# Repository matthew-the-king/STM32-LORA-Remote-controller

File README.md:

THE PROJECT
This is my LORA radio controller project! I wanted to make this because I am currently building a drone
that requires a capable LORA radio.
I have posted the Gerber files and BOM so you can produce your own functioning LORA radio controller.
The controller has two joysticks, two switches, and two potentiometers for inputs.  I also added
a buzzer to notify people when events happen, like connecting to a device.  In the PCB step file I added all the 3d 
models I could, but I could not get the potentiometer's 3d models. 

BUILDING 
To build this PCB, I would recommend ordering the PCB with a stencil because of the small and closely located parts on the board.
This PCB uses parts with pads exposed ONLY on the underside!
The PCB BOM does not include the REQUIRED RYLR998 LORA module; you can buy this on [Amazon](https://www.amazon.com/REYAX-RYLR998-Interface-Antenna-Transceiver/dp/B099RM1XMG/ref=sr_1_1?crid=3UDNJM86BEADO&dib=eyJ2IjoiMSJ9.TrUCyGx0qarh1587JZE8yvvpoC9gwe9bI9YRw3IJh5Zx1KMgEmUzJjvn7MXzx70qEOTY9Fq1M7de8QXRClEF1gXgdkHaO5Cp1hr_cBkrCVVQM3ZOe9HBNgby4LxkEoifRjcGB3QqjgsQhcNnanCQkIOsF3Hd2hs2Dmw3LSlU7O13KyXTs3yf6Vi8z0KqYX-fim7_xzP2ZXnVLrSlw5k8YtSw-LhxjmDXxdbevTJhjuQ.NWGx5ZOZ6Yl5I9t_tEakvIQr32iyknbT6vLo_iMR5xk&dib_tag=se&keywords=rylr998&qid=1781199705&sprefix=RYLR%2Caps%2C197&sr=8-1). 
Place the Lora module in these pins  with the correct orientation according to the labeled pin on the module.
Here is the BOM, but you can also find the BOM.csv file in the repository:
| Designator | Footprint | Qty | Value | LCSC Part # |
|------------|-----------|-----|-------|-------------|
| BT1 | PinHeader_1x02_P2.54mm_Vertical | 1 | Battery_Cell | |
| C1, C16 | 0402 | 2 | 10uF | |
| C10, C9 | 0603 | 2 | 18pF | |
| C11, C15, C2, C3, C4, C8 | 0402 | 6 | 0.1uF | |
| C12, C6, C7 | 0805 | 3 | 1uF | |
| C13, C14 | 0603 | 2 | 4.7uF | |
| C5 | 0603 | 1 | 10nF | |
| D1, D2 | 0805 | 2 | LED | |
| D3 | 0603 | 1 | LED | |
| D4, D5 | LED_D5.0mm | 2 | LED | |
| F1 | CP_EIA-3528-12_Kemet-T | 1 | 22uF | |
| J1 | SAMESKY_UJ20-C-H-G-SMT-1-P16-TR | 1 | USB-C | |
| J2 | PinHeader_1x05_P2.54mm_Vertical | 1 | Conn_01x05_Socket | |
| J3 | PinHeader_1x05_P2.54mm_Vertical | 1 | Conn_01x05_Pin | |
| J4 | PinHeader_1x03_P2.54mm_Vertical | 1 | Conn_01x03_Pin | |
| L1 | 0603 | 1 | 120R | |
| LS1 | SPKR_PKM22EPPH4001-B0 | 1 | PKM22EPPH4001-B0 | |
| Q1, Q2 | SOT-23 | 2 | BSS806N | |
| R1 | 0603 | 1 | 39 | |
| R10, R11 | 0402 | 2 | 1k | |
| R12 | 0603 | 1 | 49.9K | |
| R13 | 0402 | 1 | 200k | |
| R14 | 0402 | 1 | 1.13K | |
| R15, R16 | POT_P120PK-x25_TTE | 2 | P120PK | |
| R17, R18, R19, R6 | 0402 | 4 | 10k | |
| R2, R3 | 0402 | 2 | 5.1k | |
| R20, R21 | 1206 | 2 | 5M | |
| R22, R23, R8 | 0603 | 3 | 330 | |
| R4, R5 | 0402 | 2 | 22 | |
| R7 | 0603 | 1 | 2.2k | |
| R9 | 0402 | 1 | 1.18k | |
| S1, S2 | SW_200MSP1T2B4M2QE | 2 | 200MSP1T2B4M2QE | |
| U1 | UFQFPN-48_7X7X0P55MM | 1 | STM32F103CBU6 | |
| U2 | SON50P150X150X80-6N | 1 | BQ29700DSER | |
| U3, U4 | XDCR_COM-09032 | 2 | Joy_Stick | |
| U5 | SOT-23-6 | 1 | USBLC6-2SC6 | |
| U6 | SOT-223-3_TabPin2 | 1 | AMS1117-3.3 | |
| U7 | QFN50P300X300X100-17N | 1 | BQ24072TRGTR | |
| Y1 | XTAL_ECS-240-8-33-AGN-TR | 1 | ECS-80-12-33-JGN-TR | |

Once you complete your PCB, you can 3d print a case!  The case is only two parts, a Base and a top that can be screwed together with 4, 20mm screws, also the base has some holes for threaded inserts for m2.

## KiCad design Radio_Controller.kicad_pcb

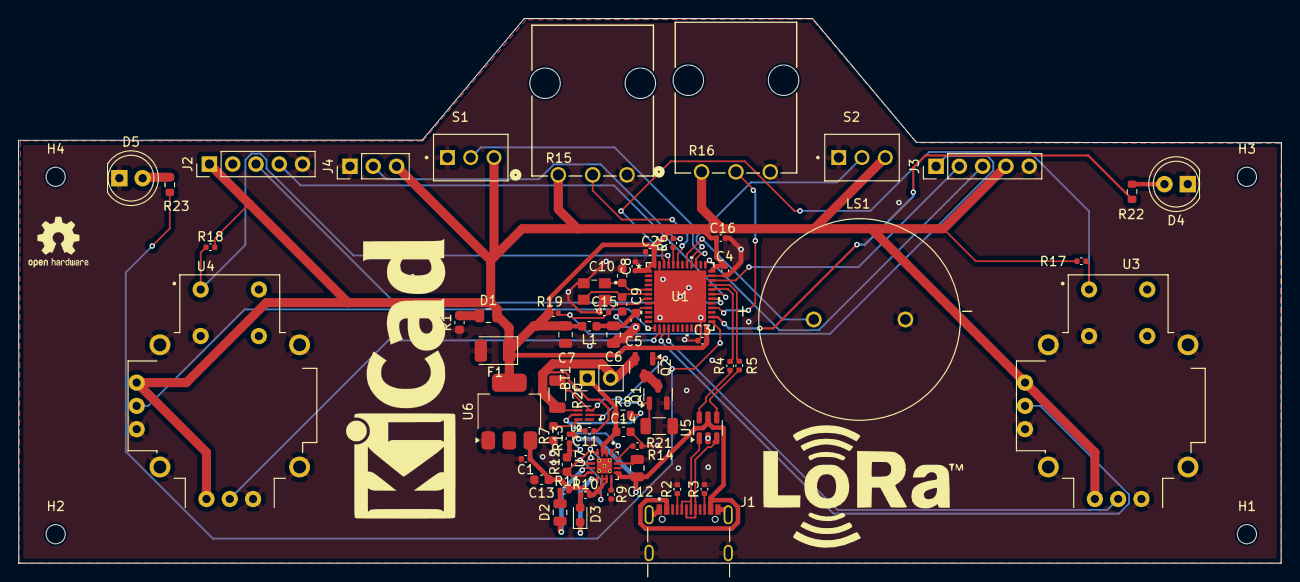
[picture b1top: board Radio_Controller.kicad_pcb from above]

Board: 2 copper layers, 137.8 x 59.4 mm, 68 parts (0 on the bottom side), 52 nets.

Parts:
BT1: Battery_Cell; PinHeader_1x02_P2.54mm_Vertical
C1, C16: 10uF; C_0402_1005Metric
C2, C3, C4, C8, C11, C15: 0.1uF; C_0402_1005Metric
C5: 10nF; C_0603_1608Metric
C6, C7, C12: 1uF; C_0805_2012Metric
C9, C10: 18pF; C_0603_1608Metric
C13, C14: 4.7uF; C_0603_1608Metric
D1, D2: LED; C_0805_2012Metric
D3: LED; LED_0603_1608Metric
D4, D5: LED; LED_D5.0mm
F1: 22uF; CP_EIA-3528-12_Kemet-T
H1, H2, H3, H4: MountingHole; MountingHole_2.1mm
J1: USB-C; SAMESKY_UJ20-C-H-G-SMT-1-P16-TR
J2: Conn_01x05_Socket; PinHeader_1x05_P2.54mm_Vertical
J3: Conn_01x05_Pin; PinHeader_1x05_P2.54mm_Vertical
J4: Conn_01x03_Pin; PinHeader_1x03_P2.54mm_Vertical
L1: 120R; C_0603_1608Metric
LS1: PKM22EPPH4001-B0; SPKR_PKM22EPPH4001-B0
Q1, Q2: BSS806N; SOT-23
R1: 39; C_0603_1608Metric
R2, R3: 5.1k; C_0402_1005Metric
R4, R5: 22; C_0402_1005Metric
R6, R17, R18, R19: 10k; C_0402_1005Metric
R7: 2.2k; C_0603_1608Metric
R8, R22, R23: 330; R_0603_1608Metric
R9: 1.18k; C_0402_1005Metric
R10, R11: 1k; C_0402_1005Metric
R12: 49.9K; C_0603_1608Metric
R13: 200k; C_0402_1005Metric
R14: 1.13K; C_0402_1005Metric
R15, R16: P120PK; POT_P120PK-x25_TTE
R20, R21: 5M; C_1206_3216Metric
S1, S2: 200MSP1T2B4M2QE; SW_200MSP1T2B4M2QE
U1: STM32F103CBU6; UFQFPN-48_7X7X0P55MM
U2: BQ29700DSER; SON50P150X150X80-6N
U3, U4: Joy_Stick; XDCR_COM-09032
U5: USBLC6-2SC6; SOT-23-6
U6: AMS1117-3.3; SOT-223-3_TabPin2
U7: BQ24072TRGTR; QFN50P300X300X100-17N
Y1: ECS-80-12-33-JGN-TR; XTAL_ECS-240-8-33-AGN-TR

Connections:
+3.3V: C2.2, C3.2, C4.2, C7.1, C8.2, C16.2, D1.2 (A), F1.1, J2.1, J3.4, J4.3, L1.2, R15.1, R16.1, R17.2, R18.2, R19.2, S1.3, S2.3, U1.1 (VBAT), U1.24 (VDD_1), U1.36 (VDD_2), U1.48 (VDD_3), U3.H1 (H+), U3.V1 (V+), U4.H1 (H+), U4.V1 (V+), U6.2 (VO)
BOOT0: J4.2, R6.2
D+: R5.2, U1.33 (PA12)
D-: R4.2, U1.32 (PA11)
GND: C1.2, C2.1, C3.1, C4.1, C5.2, C6.2, C7.2, C8.1, C9.1, C10.1, C12.2, C13.2, C14.2, C15.1, C16.1, D4.1 (K), D5.1 (K), F1.2, J1.A1_B12 (GND), J1.B1_A12 (GND__1), J1.SH1 (SHIELD), J1.SH2 (SHIELD__1), J1.SH3 (SHIELD__2), J1.SH4 (SHIELD__3), J2.5, J3.5, J4.1, LS1.N, Q1.2 (S), R1.1, R2.2, R3.2, R7.1, R9.2, R12.2, R14.2, R15.3, R16.3, R21.1, S1.1, S2.1, U1.8 (VSSA), U1.23 (VSS_1), U1.35 (VSS_2), U1.47 (VSS_3), U1.49 (EPAD), U3.B2A (SEL-), U3.H3 (H-), U3.S1 (SHIELD), U3.S2 (SHIELD__1), U3.S3 (SHIELD__2), U3.S4 (SHIELD__3), U3.V3 (V-), U4.B2A (SEL-), U4.H3 (H-), U4.S1 (SHIELD), U4.S2 (SHIELD__1), U4.S3 (SHIELD__2), U4.S4 (SHIELD__3), U4.V3 (V-), U5.2 (GND), U6.1 (GND), U7.4 (~CE), U7.6 (EN1), U7.8 (VSS), U7.15 (TD), U7.17 (EP), Y1.2 (GND), Y1.4 (GND__1)
H1: U1.14 (PA4), U4.H2 (H)
H2: U1.16 (PA6), U3.H2 (H)
NRST: C15.2, J3.1, R19.1, U1.7 (NRST)
unnamed: BT1.2 (-), C11.2, Q2.2 (S), R20.2, U2.4 (VSS)
unnamed: D1.1 (K), R1.2
unnamed: D2.2 (A), R11.1
unnamed: D2.1 (K), U7.7 (~PGOOD)
unnamed: D3.2 (A), R10.1
unnamed: D3.1 (K), U7.9 (~CHG)
unnamed: D4.2 (A), R22.1
unnamed: D5.2 (A), R23.2
unnamed: J1.A5 (CC1), R2.1
unnamed: J1.B5 (CC2), R3.1
unnamed: J1.A7 (DN1), J1.B7 (DN2), U5.1 (I/O1)
unnamed: J1.A6 (DP1), J1.B6 (DP2), U5.3 (I/O2)
unnamed: Q1.3 (D), Q2.3 (D)
unnamed: Q1.1 (G), R21.2, U2.2 (COUT)
unnamed: Q2.1 (G), R20.1, U2.3 (DOUT)
unnamed: R4.1, U5.6 (I/O1)
unnamed: R5.1, U5.4 (I/O2)
unnamed: R6.1, U1.44 (BOOT0)
unnamed: S1.2, U1.39 (PB3)
unnamed: S2.2, U1.40 (PB4)
unnamed: LS1.P, U1.41 (PB5)
unnamed: R15.2, U1.43 (PB7)
unnamed: R23.1, U1.25 (PB12)
unnamed: R22.2, U1.26 (PB13)
unnamed: R16.2, U1.28 (PB15)
unnamed: C5.1, C6.1, L1.1, U1.9 (VDDA)
unnamed: C11.1, R8.2, U2.5 (BAT)
unnamed: R7.2, U2.6 (V-)
unnamed: R9.1, U7.12 (ILIM)
unnamed: R14.1, U7.16 (ISET)
unnamed: R12.1, R13.2, U7.1 (TS)
OSC_IN: C10.2, U1.5 (OSC_IN), Y1.1 (IN/OUT)
OSC_OUT: C9.2, U1.6 (OSC_OUT), Y1.3 (OUT/IN)
OUT: C1.1, C13.1, R10.2, R11.2, U6.3 (VI), U7.5 (EN2), U7.10 (OUT), U7.11 (OUT__1)
Pack+: BT1.1 (+), C14.1, R8.1, U7.2 (BAT), U7.3 (BAT__1)
RX: J2.3, U1.30 (PA9)
SEL1: R18.1, U1.45 (PB8), U4.B1A (SEL+)
SEL2: R17.1, U1.46 (PB9), U3.B1A (SEL+)
SWCLK: J3.3, U1.37 (PA14)
SWDIO: J3.2, U1.34 (PA13)
TX: J2.4, U1.31 (PA10)
V1: U1.13 (PA3), U4.V2 (V)
V2: U1.15 (PA5), U3.V2 (V)
VBUS: C12.1, J1.A4_B9 (VBUS), J1.B4_A9 (VBUS__1), R13.1, U5.5 (VBUS), U7.13 (IN)

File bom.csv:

Designator,Footprint,Quantity,Value,LCSC Part #
BT1,PinHeader_1x02_P2.54mm_Vertical,1,Battery_Cell,
"C1, C16",0402,2,10uF,
"C10, C9",0603,2,18pF,
"C11, C15, C2, C3, C4, C8",0402,6,0.1uF,
"C12, C6, C7",0805,3,1uF,
"C13, C14",0603,2,4.7uF,
C5,0603,1,10nF,
"D1, D2",0805,2,LED,
D3,0603,1,LED,
F1,CP_EIA-3528-12_Kemet-T,1,22uF,
J1,SAMESKY_UJ20-C-H-G-SMT-1-P16-TR,1,USB-C,
J2,PinHeader_1x05_P2.54mm_Vertical,1,Conn_01x05_Socket,
J3,PinHeader_1x05_P2.54mm_Vertical,1,Conn_01x05_Pin,
J4,PinHeader_1x03_P2.54mm_Horizontal,1,Conn_01x03_Pin,
L1,0603,1,120R,
LS1,SPKR_PKM22EPPH4001-B0,1,PKM22EPPH4001-B0,
"Q1, Q2",SOT-23,2,BSS806N,
R1,0603,1,39,
"R10, R11",0402,2,1k,
R12,0603,1,49.9K,
R13,0402,1,200k,
R14,0402,1,1.13K,
"R15, R16",POT_P120PK-x25_TTE,2,P120PK,
"R17, R18, R19, R6",0402,4,10k,
"R2, R3",0402,2,5.1k,
"R20, R21",1206,2,5M,
"R4, R5",0402,2,22,
R7,0603,1,2.2k,
R8,0603,1,330,
R9,0402,1,1.18k,
"S1, S2",SW_200MSP1T2B4M2QE,2,200MSP1T2B4M2QE,
U1,UFQFPN-48_7X7X0P55MM,1,STM32F103CBU6,
U2,SON50P150X150X80-6N,1,BQ29700DSER,
"U3, U4",XDCR_COM-09032,2,Joy_Stick,
U5,SOT-23-6,1,USBLC6-2SC6,
U6,SOT-223-3_TabPin2,1,AMS1117-3.3,
U7,QFN50P300X300X100-17N,1,BQ24072TRGTR,
Y1,XTAL_ECS-240-8-33-AGN-TR,1,ECS-80-12-33-JGN-TR,

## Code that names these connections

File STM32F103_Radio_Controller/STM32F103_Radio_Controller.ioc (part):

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Mcu.Name=STM32F103CBUx
Mcu.Package=UFQFPN48
Mcu.UserName=STM32F103CBUx
PA10.Mode=Asynchronous
PA10.Signal=USART1_RX
PA11.Mode=Device
PA11.Signal=USB_DM
PA12.Mode=Device
PA12.Signal=USB_DP
PA13.Mode=Serial_Wire
PA13.Signal=SYS_JTMS-SWDIO
PA14.Mode=Serial_Wire
PA14.Signal=SYS_JTCK-SWCLK
PA3.Signal=ADCx_IN3
PA4.Signal=ADCx_IN4
PA5.Signal=ADCx_IN5
PA6.Signal=ADCx_IN6
PA9.Mode=Asynchronous
PA9.Signal=USART1_TX
PB3.Signal=GPIO_Input
PB4.Signal=GPIO_Input
PD0-OSC_IN.Mode=HSE-External-Oscillator
PD0-OSC_IN.Signal=RCC_OSC_IN
PD1-OSC_OUT.Mode=HSE-External-Oscillator
PD1-OSC_OUT.Signal=RCC_OSC_OUT
RCC.SYSCLKFreq_VALUE=48000000
RCC.SYSCLKSource=RCC_SYSCLKSOURCE_PLLCLK
board=custom

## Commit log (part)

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2026-06-07 Add project description to README
2026-06-11 Enhance README with project details and build info
    Expanded project description and added building instructions.
2026-06-11 PCB files
2026-06-11 Fix typo in LORA module name in README
2026-06-11 Radio Controller shell
2026-06-12 Enhance README with project details and BOM
    Added detailed project description and BOM table.
2026-06-12 Enhance README with BOM details
    Added detailed BOM table with component specifications.
2026-06-12 Organize files
2026-06-12 Added CAD back
2026-06-12 moved README
2026-06-16 switched PCB cad into CAD folder
2026-06-16 Update README with project details and case design
    Added details about the project, including the case design and 3D models.
2026-06-16 Fix punctuation in case assembly instructions
2026-06-16 delted STL files for STEP files
